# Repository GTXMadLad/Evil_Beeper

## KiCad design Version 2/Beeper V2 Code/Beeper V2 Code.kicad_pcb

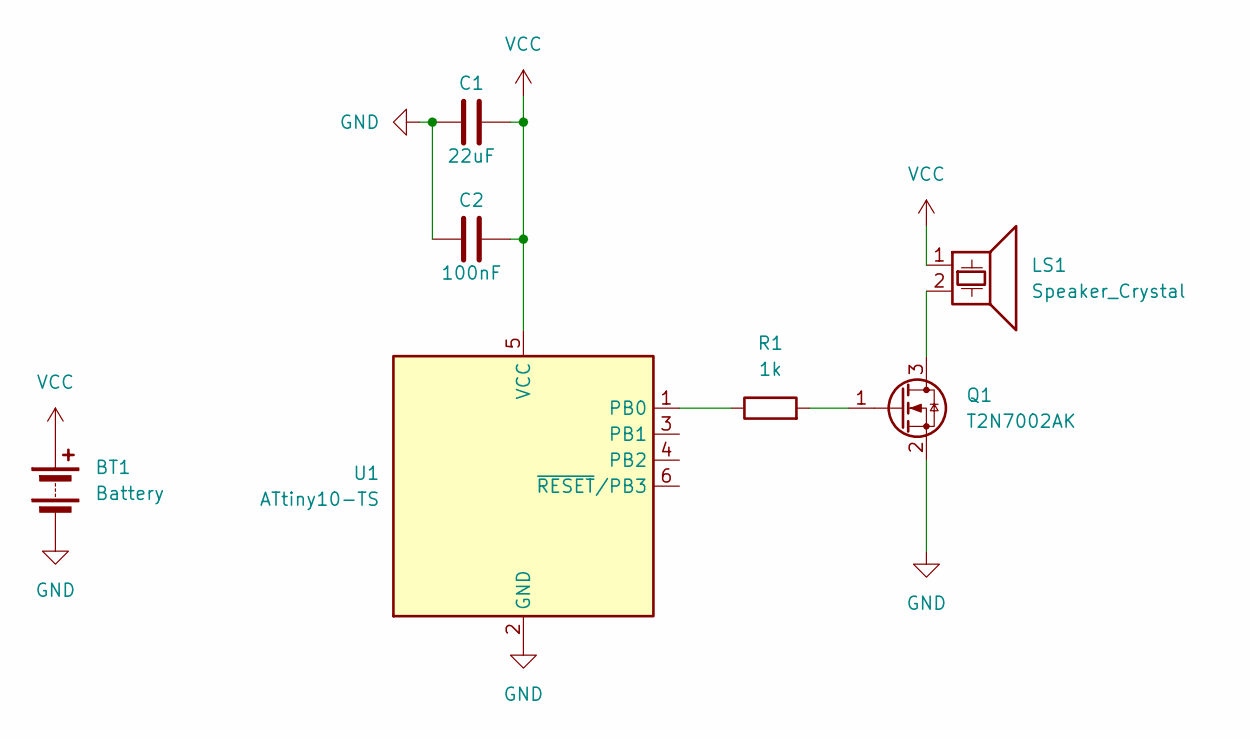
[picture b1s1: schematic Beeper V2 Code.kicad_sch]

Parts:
BT1: Battery; 2032 Battery Holder
C1: 22uF; C_0805_2012Metric_Pad1.18x1.45mm_HandSolder
C2: 100nF; C_0805_2012Metric_Pad1.18x1.45mm_HandSolder
LS1: Speaker_Crystal; Buzzer
Q1: T2N7002AK; SOT-23
R1: 1k; R_0805_2012Metric_Pad1.20x1.40mm_HandSolder
U1: ATtiny10-TS; SOT-23-6

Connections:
GND: BT1.2 (-), C1.1, C2.1, Q1.2 (S), U1.2 (GND)
unnamed: LS1.2, Q1.3 (D)
unnamed: Q1.1 (G), R1.2
unnamed: R1.1, U1.1 (PB0)
VCC: BT1.1 (+), C1.2, C2.2, LS1.1, U1.5 (VCC)

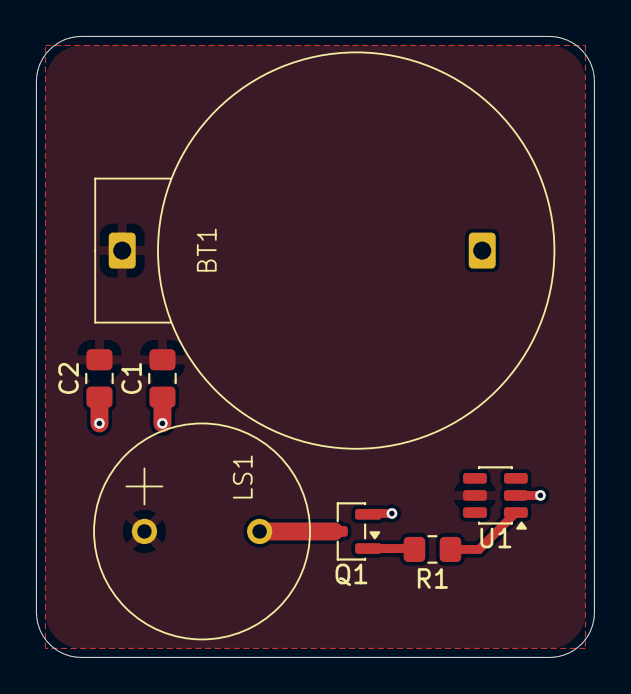
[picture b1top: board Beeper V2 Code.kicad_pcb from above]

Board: 2 copper layers, 31.0 x 34.5 mm, 7 parts (0 on the bottom side), 5 nets.

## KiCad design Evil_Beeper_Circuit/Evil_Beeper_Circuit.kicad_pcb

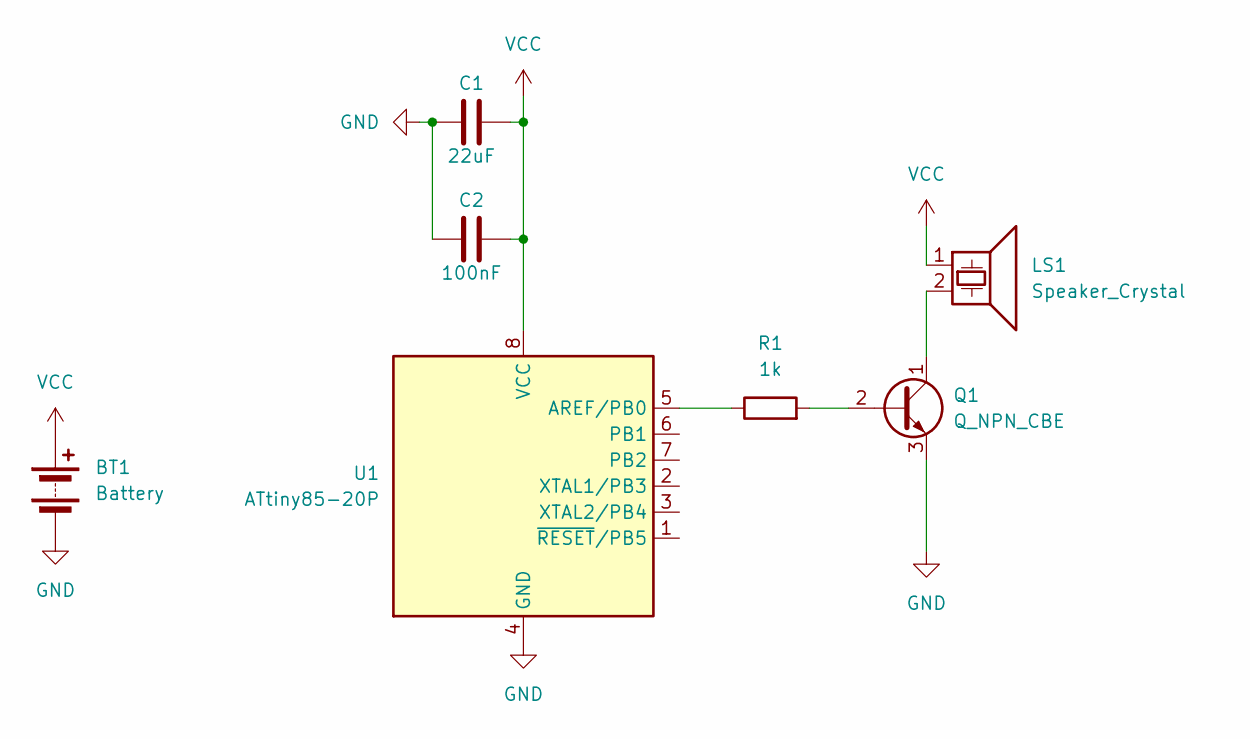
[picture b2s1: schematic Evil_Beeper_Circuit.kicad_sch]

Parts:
BT1: Battery; 2032 Battery Holder
C1: 22uF; CP_Radial_D4.0mm_P1.50mm
C2: 100nF; C_Rect_L7.2mm_W3.0mm_P5.00mm_FKS2_FKP2_MKS2_MKP2
LS1: Speaker_Crystal; Buzzer
Q1: Q_NPN_CBE; TO-92_Inline
R1: 1k; R_Axial_DIN0207_L6.3mm_D2.5mm_P7.62mm_Horizontal
U1: ATtiny85-20P; DIP-8_W7.62mm_Socket

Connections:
GND: BT1.2 (-), C1.1, C2.1, Q1.3 (E), U1.4 (GND)
unnamed: Q1.2 (B), R1.2
unnamed: LS1.2, Q1.1 (C)
unnamed: R1.1, U1.5 (AREF/PB0)
VCC: BT1.1 (+), C1.2, C2.2, LS1.1, U1.8 (VCC)

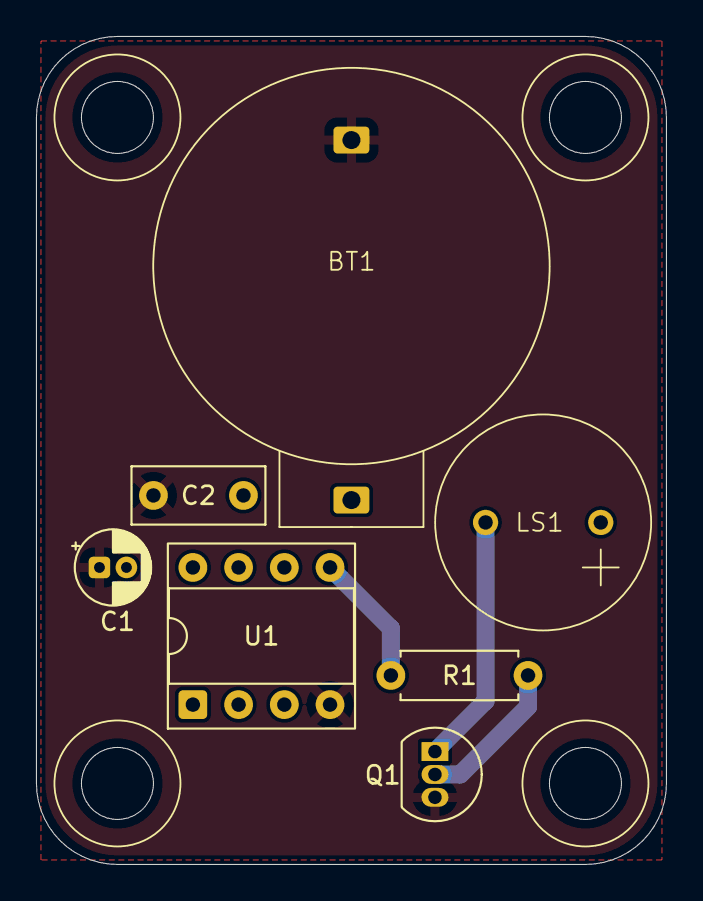
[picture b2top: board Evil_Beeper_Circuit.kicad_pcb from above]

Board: 2 copper layers, 35.0 x 46.0 mm, 7 parts (0 on the bottom side), 5 nets.

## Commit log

2026-02-27 added code folder
2026-02-27 added attiny to schematic
2026-03-02 added circuit components
2026-03-08 Designed PCB
2026-03-09 Version for PCB Manufacture
2026-03-09 Fixed Corners
2026-03-09 More small edits
2026-04-21 added v2
2026-04-22 routed new smd design
